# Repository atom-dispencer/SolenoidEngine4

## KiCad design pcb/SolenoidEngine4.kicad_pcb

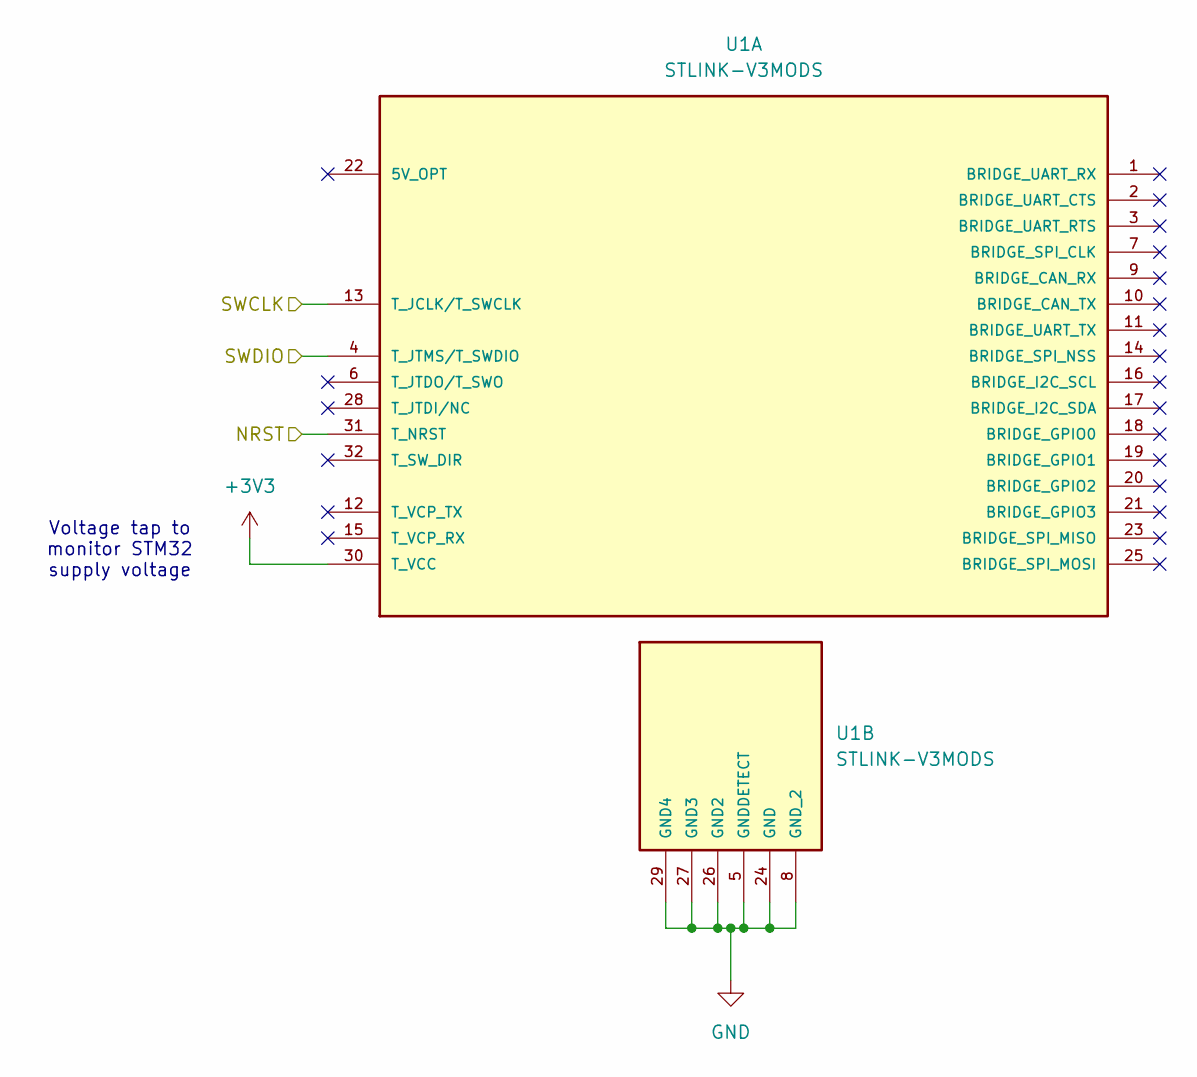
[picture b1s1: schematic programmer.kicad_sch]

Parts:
U1: STLINK-V3MODS; STLINK_V3MODS; PARTREV 1

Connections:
+3V3: U1.30 (T_VCC); also elsewhere on the board
/Microcontroller/NRST: U1.31 (T_NRST); also elsewhere on the board
/Microcontroller/SWCLK: U1.13 (T_JCLK/T_SWCLK); also elsewhere on the board
/Microcontroller/SWDIO: U1.4 (T_JTMS/T_SWDIO); also elsewhere on the board
GND: U1.5 (GNDDETECT), U1.8 (GND_2), U1.24 (GND), U1.26 (GND2), U1.27 (GND3), U1.29 (GND4); also elsewhere on the board

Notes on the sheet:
Voltage tap to monitor STM32 supply voltage

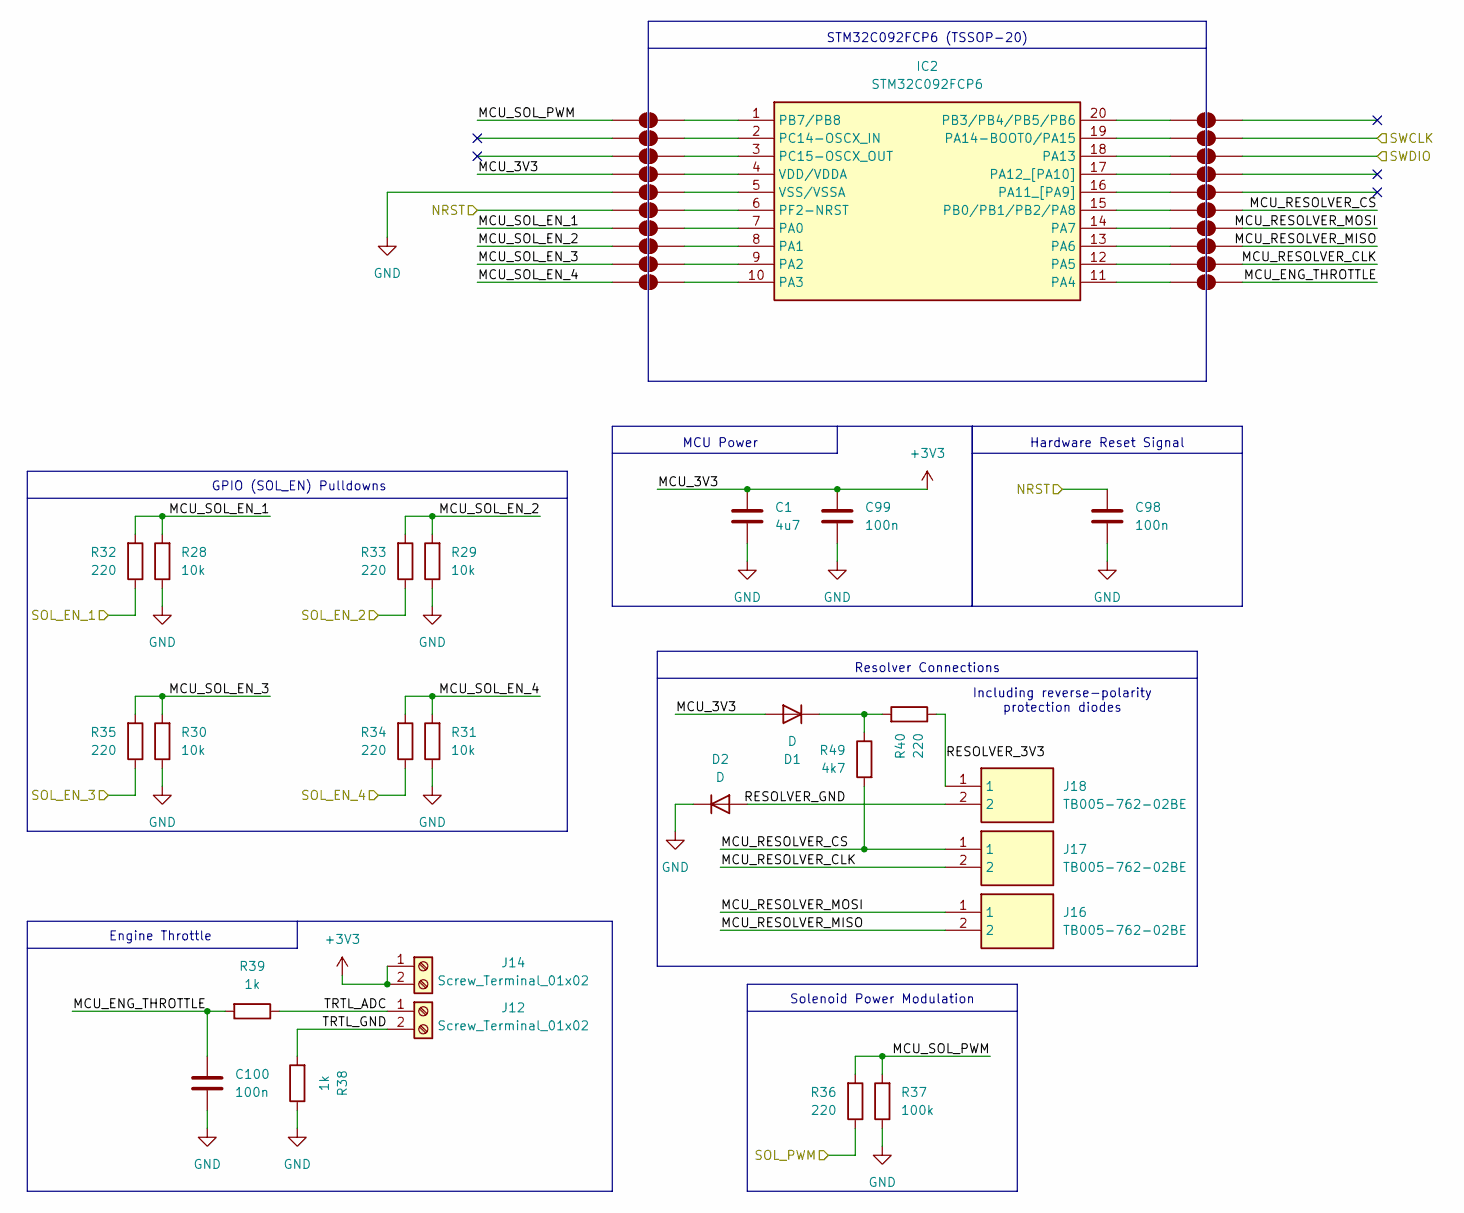
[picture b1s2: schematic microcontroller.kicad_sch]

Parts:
C1: 4u7; C_0805_2012Metric
C98: 100n; C_0603_1608Metric
C99, C100: 100n; C_0805_2012Metric
D1, D2: D; D_0805_2012Metric
IC2: STM32C092FCP6; SOP65P640X120-20N; Manufacturer_Part_Number STM32C092FCP6
J12, J14: Screw_Terminal_01x02; TB005-762-02BE
J16, J17, J18: TB005-762-02BE; Mouser Part Number 490-TB005-762-02BE
JP1, JP2, JP3, JP4, JP5, JP6, JP7, JP8, JP9, JP10, JP11, JP12, JP13, JP14, JP15, JP16, JP17, JP18, JP19, JP20: SolderJumper_2_Open; SolderJumper-2_P1.3mm_Open_TrianglePad1.0x1.5mm
R28, R29, R30, R31: 10k; R_0805_2012Metric
R32, R33, R34, R35, R36, R40: 220; R_0805_2012Metric
R37: 100k; R_0805_2012Metric
R38, R39: 1k; R_0805_2012Metric
R49: 4k7; R_0805_2012Metric

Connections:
+3V3: C1.1, C99.1, D1.2 (A), J14.1, J14.2, JP14.1 (A); also elsewhere on the board
/Microcontroller/MCU_ENG_THROTTLE: C100.1, JP10.2 (B), R39.2
/Microcontroller/MCU_RESOLVER_CLK: J17.2, JP9.2 (B)
/Microcontroller/MCU_RESOLVER_CS: J17.1, JP6.2 (B), R49.2
/Microcontroller/MCU_RESOLVER_MISO: J16.2, JP8.2 (B)
/Microcontroller/MCU_RESOLVER_MOSI: J16.1, JP7.2 (B)
/Microcontroller/MCU_SOL_EN_1: JP17.1 (A), R28.2, R32.2
/Microcontroller/MCU_SOL_EN_2: JP18.1 (A), R29.2, R33.2
/Microcontroller/MCU_SOL_EN_3: JP19.1 (A), R30.2, R35.2
/Microcontroller/MCU_SOL_EN_4: JP20.1 (A), R31.2, R34.2
/Microcontroller/MCU_SOL_PWM: JP11.1 (A), R36.2, R37.2
/Microcontroller/NRST: C98.1, JP16.1 (A); also elsewhere on the board
/Microcontroller/RESOLVER_3V3: J18.1, R40.1
/Microcontroller/RESOLVER_GND: D2.2 (A), J18.2
/Microcontroller/SOL_EN_1: R32.1; also elsewhere on the board
/Microcontroller/SOL_EN_2: R33.1; also elsewhere on the board
/Microcontroller/SOL_EN_3: R35.1; also elsewhere on the board
/Microcontroller/SOL_EN_4: R34.1; also elsewhere on the board
/Microcontroller/SOL_PWM: R36.1; also elsewhere on the board
/Microcontroller/SWCLK: JP2.2 (B); also elsewhere on the board
/Microcontroller/SWDIO: JP3.2 (B); also elsewhere on the board
/Microcontroller/TRTL_ADC: J12.1, R39.1
/Microcontroller/TRTL_GND: J12.2, R38.2
GND: C1.2, C98.2, C99.2, C100.2, D2.1 (K), JP15.1 (A), R28.1, R29.1, R30.1, R31.1, R37.1, R38.1; also elsewhere on the board
unnamed: D1.1 (K), R40.2, R49.1
unnamed: IC2.7 (PA0), JP17.2 (B)
unnamed: IC2.8 (PA1), JP18.2 (B)
unnamed: IC2.9 (PA2), JP19.2 (B)
unnamed: IC2.10 (PA3), JP20.2 (B)
unnamed: IC2.11 (PA4), JP10.1 (A)
unnamed: IC2.12 (PA5), JP9.1 (A)
unnamed: IC2.13 (PA6), JP8.1 (A)
unnamed: IC2.14 (PA7), JP7.1 (A)
unnamed: IC2.16 (PA11_[PA9]), JP5.1 (A_1)
unnamed: IC2.17 (PA12_[PA10]), JP4.1 (A_1)
unnamed: IC2.18 (PA13), JP3.1 (A)
unnamed: IC2.19 (PA14-BOOT0/PA15), JP2.1 (A)
unnamed: IC2.15 (PB0/PB1/PB2/PA8), JP6.1 (A)
unnamed: IC2.20 (PB3/PB4/PB5/PB6), JP1.1 (A_1)
unnamed: IC2.1 (PB7/PB8), JP11.2 (B)
unnamed: IC2.2 (PC14-OSCX_IN), JP12.2 (B_2)
unnamed: IC2.3 (PC15-OSCX_OUT), JP13.2 (B_2)
unnamed: IC2.6 (PF2-NRST), JP16.2 (B)
unnamed: IC2.4 (VDD/VDDA), JP14.2 (B)
unnamed: IC2.5 (VSS/VSSA), JP15.2 (B)

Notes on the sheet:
Solenoid Power Modulation
STM32C092FCP6 (TSSOP-20)
Hardware Reset Signal
Including reverse-polarity protection diodes
Engine Throttle
MCU Power
GPIO (SOL_EN) Pulldowns
Resolver Connections

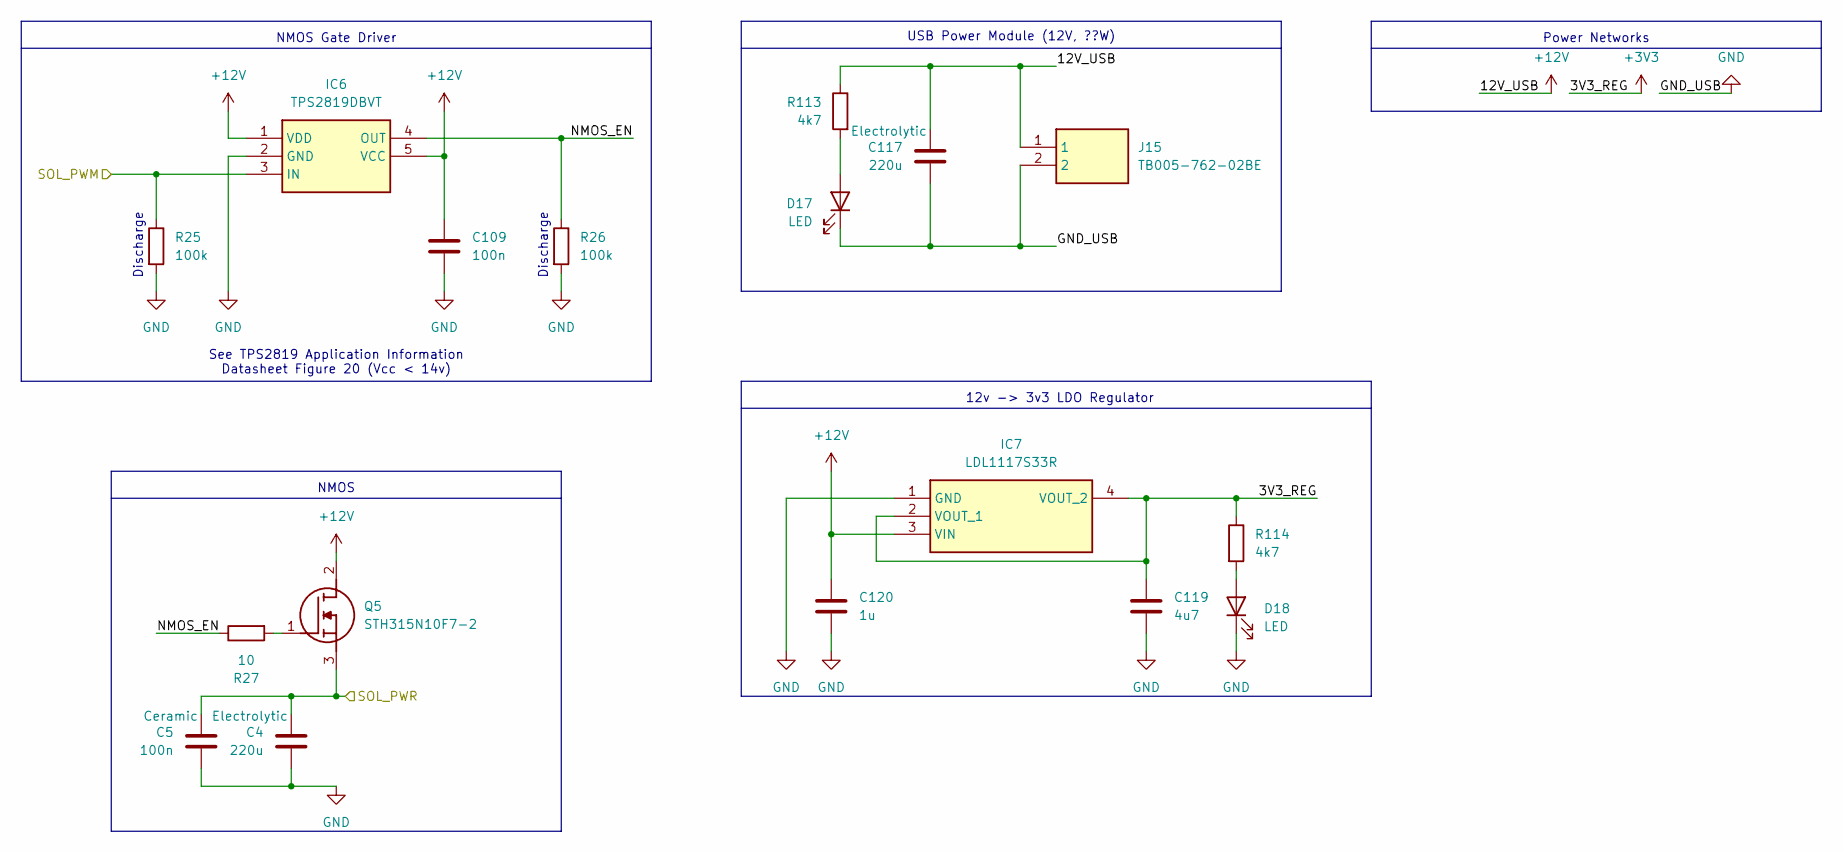
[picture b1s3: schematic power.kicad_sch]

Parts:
C4, C117: 220u; CP_Elec_10x10
C5, C109: 100n; C_0805_2012Metric
C119: 4u7; C_0805_2012Metric
C120: 1u; C_0805_2012Metric
D17, D18: LED; D_0805_2012Metric
IC6: TPS2819DBVT; SOT95P280X145-5N; Mouser Part Number 595-TPS2819DBVT
IC7: LDL1117S33R; SOT230P700X180-4N; Mouser Part Number 511-LDL1117S33R
J15: TB005-762-02BE; Mouser Part Number 490-TB005-762-02BE
Q5: STH315N10F7-2; STH315N10F72; Mouser Part Number 511-STH315N10F7-2
R25, R26: 100k; R_0805_2012Metric
R27: 10; R_0805_2012Metric
R113, R114: 4k7; R_0805_2012Metric

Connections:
+3V3: C119.1, IC7.2 (VOUT_1), IC7.4 (VOUT_2), R114.1; also elsewhere on the board
+12V: C109.1, C117.1, C120.1, IC6.1 (VDD), IC6.5 (VCC), IC7.3 (VIN), J15.1, Q5.2 (D), R113.1; also elsewhere on the board
/Microcontroller/SOL_PWM: IC6.3 (IN), R25.1; also elsewhere on the board
/Power/NMOS_EN: IC6.4 (OUT), R26.1, R27.1
/Solenoids/Solenoid 1/SOL+: C4.1, C5.1, Q5.3 (S); also elsewhere on the board
GND: C4.2, C5.2, C109.2, C117.2, C119.2, C120.2, D17.1 (K), D18.1 (K), IC6.2 (GND), IC7.1 (GND), J15.2, R25.2, R26.2; also elsewhere on the board
unnamed: D17.2 (A), R113.2
unnamed: D18.2 (A), R114.2
unnamed: Q5.1 (G), R27.2

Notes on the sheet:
Power Networks
USB Power Module (12V, ??W)
12v -> 3v3 LDO Regulator
See TPS2819 Application Information Datasheet Figure 20 (Vcc < 14v)
Discharge
NMOS
NMOS Gate Driver

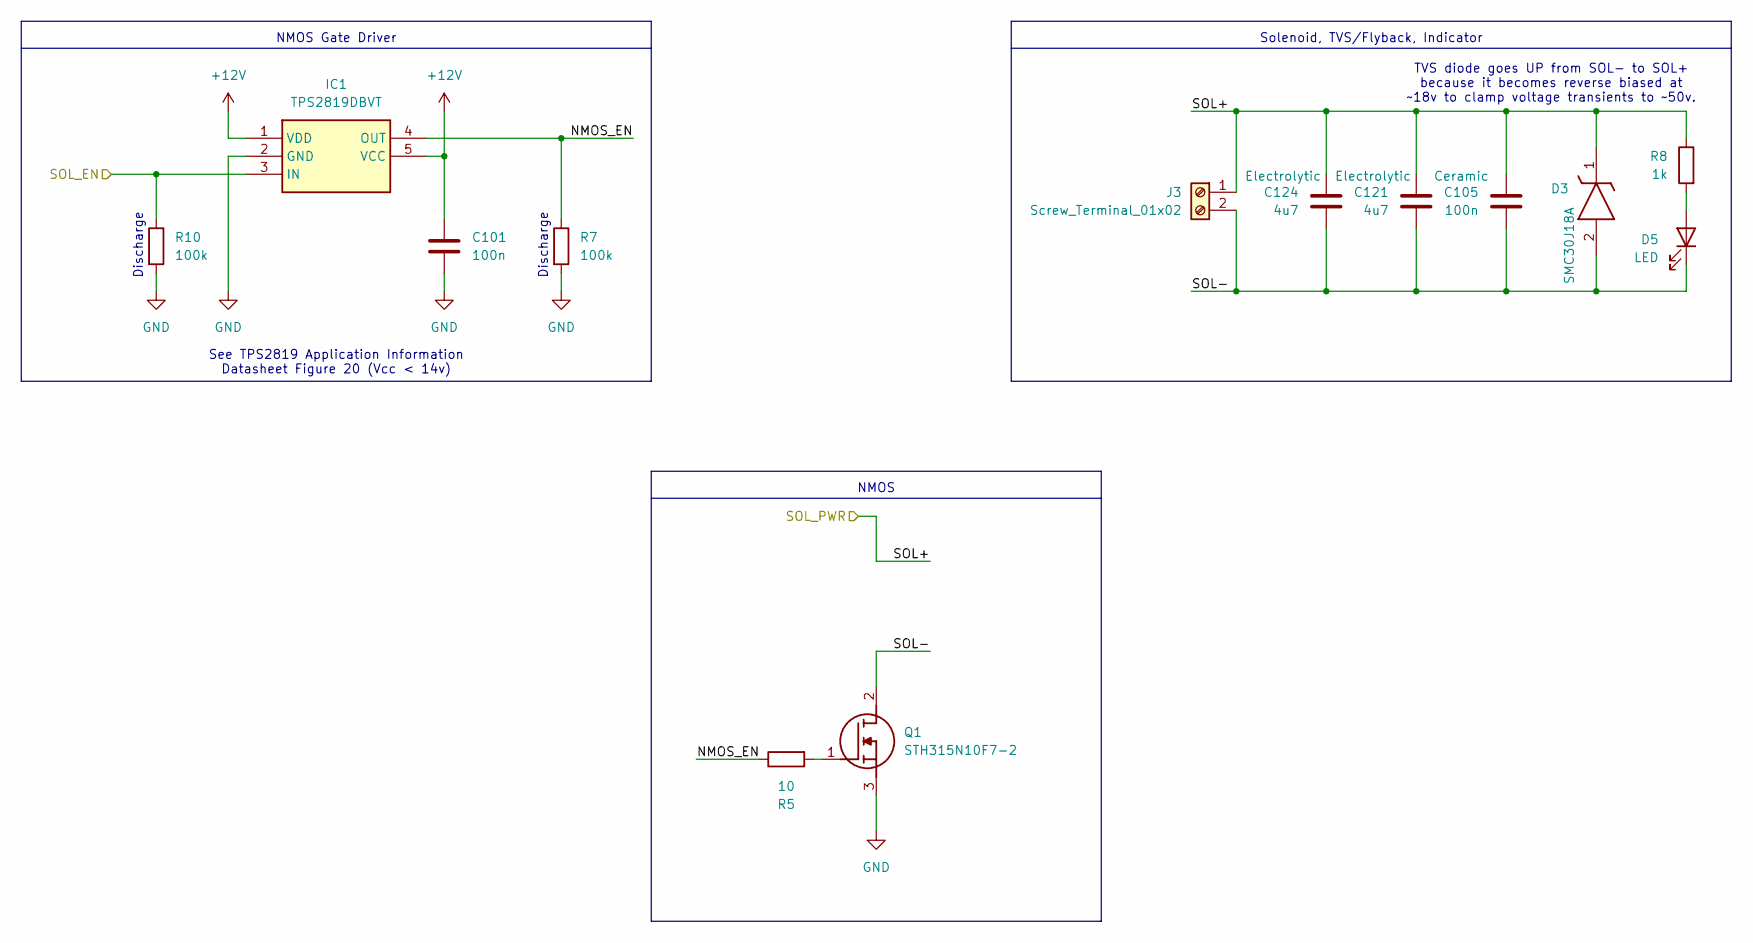
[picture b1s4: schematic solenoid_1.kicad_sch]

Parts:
C101, C105: 100n; C_0805_2012Metric
C121, C124: 4u7; C_0805_2012Metric
D3: SMC30J18A; DIOM8059X265N; Manufacturer_Part_Number SMC30J18A
D5: LED; D_0805_2012Metric
IC1: TPS2819DBVT; SOT95P280X145-5N; Mouser Part Number 595-TPS2819DBVT
J3: Screw_Terminal_01x02; TB005-762-02BE
Q1: STH315N10F7-2; STH315N10F72; Mouser Part Number 511-STH315N10F7-2
R5: 10; R_0805_2012Metric
R7, R10: 100k; R_0805_2012Metric
R8: 1k; R_0805_2012Metric

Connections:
+12V: C101.1, IC1.1 (VDD), IC1.5 (VCC); also elsewhere on the board
/Microcontroller/SOL_EN_1: IC1.3 (IN), R10.1; also elsewhere on the board
/Solenoids/Solenoid 1/NMOS_EN: IC1.4 (OUT), R5.1, R7.1
/Solenoids/Solenoid 1/SOL+: C105.1, C121.1, C124.1, D3.1 (K), J3.1, R8.1; also elsewhere on the board
/Solenoids/Solenoid 1/SOL-: C105.2, C121.2, C124.2, D3.2 (A), D5.1 (K), J3.2, Q1.2 (D)
GND: C101.2, IC1.2 (GND), Q1.3 (S), R7.2, R10.2; also elsewhere on the board
unnamed: D5.2 (A), R8.2
unnamed: Q1.1 (G), R5.2

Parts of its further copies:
C102, C103, C104, C106, C107, C108: 100n; C_0805_2012Metric
C122, C123, C125, C126, C127, C128: 4u7; C_0805_2012Metric
D4, D6, D8: SMC30J18A; DIOM8059X265N; Manufacturer_Part_Number SMC30J18A
D7, D9, D11: LED; D_0805_2012Metric
IC3, IC4, IC5: TPS2819DBVT; SOT95P280X145-5N; Mouser Part Number 595-TPS2819DBVT
J7, J10, J13: Screw_Terminal_01x02; TB005-762-02BE
Q2, Q3, Q4: STH315N10F7-2; STH315N10F72; Mouser Part Number 511-STH315N10F7-2
R6, R18, R23: 10; R_0805_2012Metric
R12, R13, R16, R17, R21, R22: 100k; R_0805_2012Metric
R14, R19, R24: 1k; R_0805_2012Metric

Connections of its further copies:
+12V: C102.1, C103.1, C104.1, IC3.1 (VDD), IC3.5 (VCC), IC4.1 (VDD), IC4.5 (VCC), IC5.1 (VDD), IC5.5 (VCC); also elsewhere on the board
/Microcontroller/SOL_EN_2: IC3.3 (IN), R12.1; also elsewhere on the board
/Microcontroller/SOL_EN_3: IC4.3 (IN), R16.1; also elsewhere on the board
/Microcontroller/SOL_EN_4: IC5.3 (IN), R21.1; also elsewhere on the board
/Solenoids/Solenoid 1/SOL+: C106.1, C107.1, C108.1, C122.1, C123.1, C125.1, C126.1, C127.1, C128.1, D4.1 (K), D6.1 (K), D8.1 (K), J7.1, J10.1, J13.1, R14.1, R19.1, R24.1; also elsewhere on the board
/Solenoids/Solenoid 2/NMOS_EN: IC3.4 (OUT), R6.1, R13.1
/Solenoids/Solenoid 2/SOL-: C106.2, C122.2, C125.2, D4.2 (A), D7.1 (K), J7.2, Q2.2 (D)
/Solenoids/Solenoid 3/NMOS_EN: IC4.4 (OUT), R17.1, R18.1
/Solenoids/Solenoid 3/SOL-: C107.2, C123.2, C126.2, D6.2 (A), D9.1 (K), J10.2, Q3.2 (D)
/Solenoids/Solenoid 4/NMOS_EN: IC5.4 (OUT), R22.1, R23.1
/Solenoids/Solenoid 4/SOL-: C108.2, C127.2, C128.2, D8.2 (A), D11.1 (K), J13.2, Q4.2 (D)
GND: C102.2, C103.2, C104.2, IC3.2 (GND), IC4.2 (GND), IC5.2 (GND), Q2.3 (S), Q3.3 (S), Q4.3 (S), R12.2, R13.2, R16.2, R17.2, R21.2, R22.2; also elsewhere on the board
unnamed: D7.2 (A), R14.2
unnamed: D9.2 (A), R19.2
unnamed: D11.2 (A), R24.2
unnamed: Q2.1 (G), R6.2
unnamed: Q3.1 (G), R18.2
unnamed: Q4.1 (G), R23.2

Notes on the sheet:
Discharge
TVS diode goes UP from SOL- to SOL+ because it becomes reverse biased at ~18v to clamp voltage transients to ~50v.
NMOS Gate Driver
Solenoid, TVS/Flyback, Indicator
NMOS
See TPS2819 Application Information Datasheet Figure 20 (Vcc < 14v)

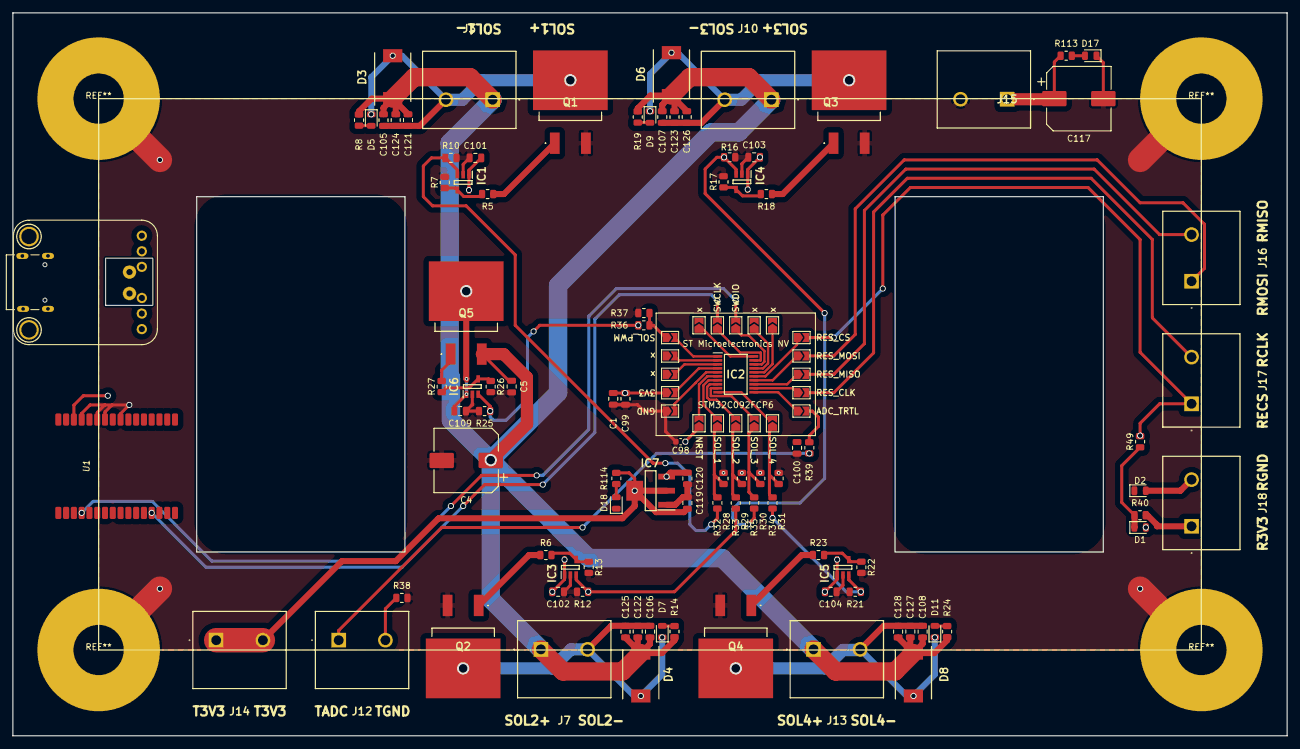
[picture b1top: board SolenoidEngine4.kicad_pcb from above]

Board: 4 copper layers, 208.0 x 118.0 mm, 116 parts (0 on the bottom side), 67 nets.

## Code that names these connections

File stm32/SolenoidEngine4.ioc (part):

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Mcu.Name=STM32C092FCPx
Mcu.Package=TSSOP20
Mcu.UserName=STM32C092FCPx
PA0.GPIOParameters=GPIO_Label
PA0.GPIO_Label=SOL_EN_1
PA0.Signal=GPIO_Output
PA1.GPIOParameters=GPIO_Label
PA1.GPIO_Label=SOL_EN_2
PA1.Signal=GPIO_Output
PA13.Mode=Serial_Wire
PA13.Signal=DEBUG_SWDIO
PA14-BOOT0.Mode=Serial_Wire
PA14-BOOT0.Signal=DEBUG_SWCLK
PA14-BOOT0__PA15.StandardMode=true
PA2.GPIOParameters=GPIO_Label
PA2.GPIO_Label=SOL_EN_3
PA2.Signal=GPIO_Output
PA3.GPIOParameters=GPIO_Label
PA3.GPIO_Label=SOL_EN_4
PA3.Signal=GPIO_Output
PA4.GPIOParameters=GPIO_Label
PA4.GPIO_Label=ENG_THROTTLE
PA4.Mode=IN4
PA4.Signal=ADC1_IN4
PA5.Mode=Full_Duplex_Master
PA5.Signal=SPI1_SCK
PA6.Mode=Full_Duplex_Master
PA6.Signal=SPI1_MISO
PA7.Mode=Full_Duplex_Master
PA7.Signal=SPI1_MOSI
PB0.Mode=NSS_Signal_Hard_Output
PB0.Signal=SPI1_NSS
PB0__PB1__PB2__PA8.StandardMode=true
PB3__PB4__PB5__PB6.StandardMode=true
PB7.GPIOParameters=GPIO_Label
PB7.GPIO_Label=SOL_PWM
PB7.Signal=S_TIM16_CH1
PB7__PB8.StandardMode=true
RCC.HSE_VALUE=8000000
RCC.SYSCLKFreq_VALUE=48000000
board=custom
